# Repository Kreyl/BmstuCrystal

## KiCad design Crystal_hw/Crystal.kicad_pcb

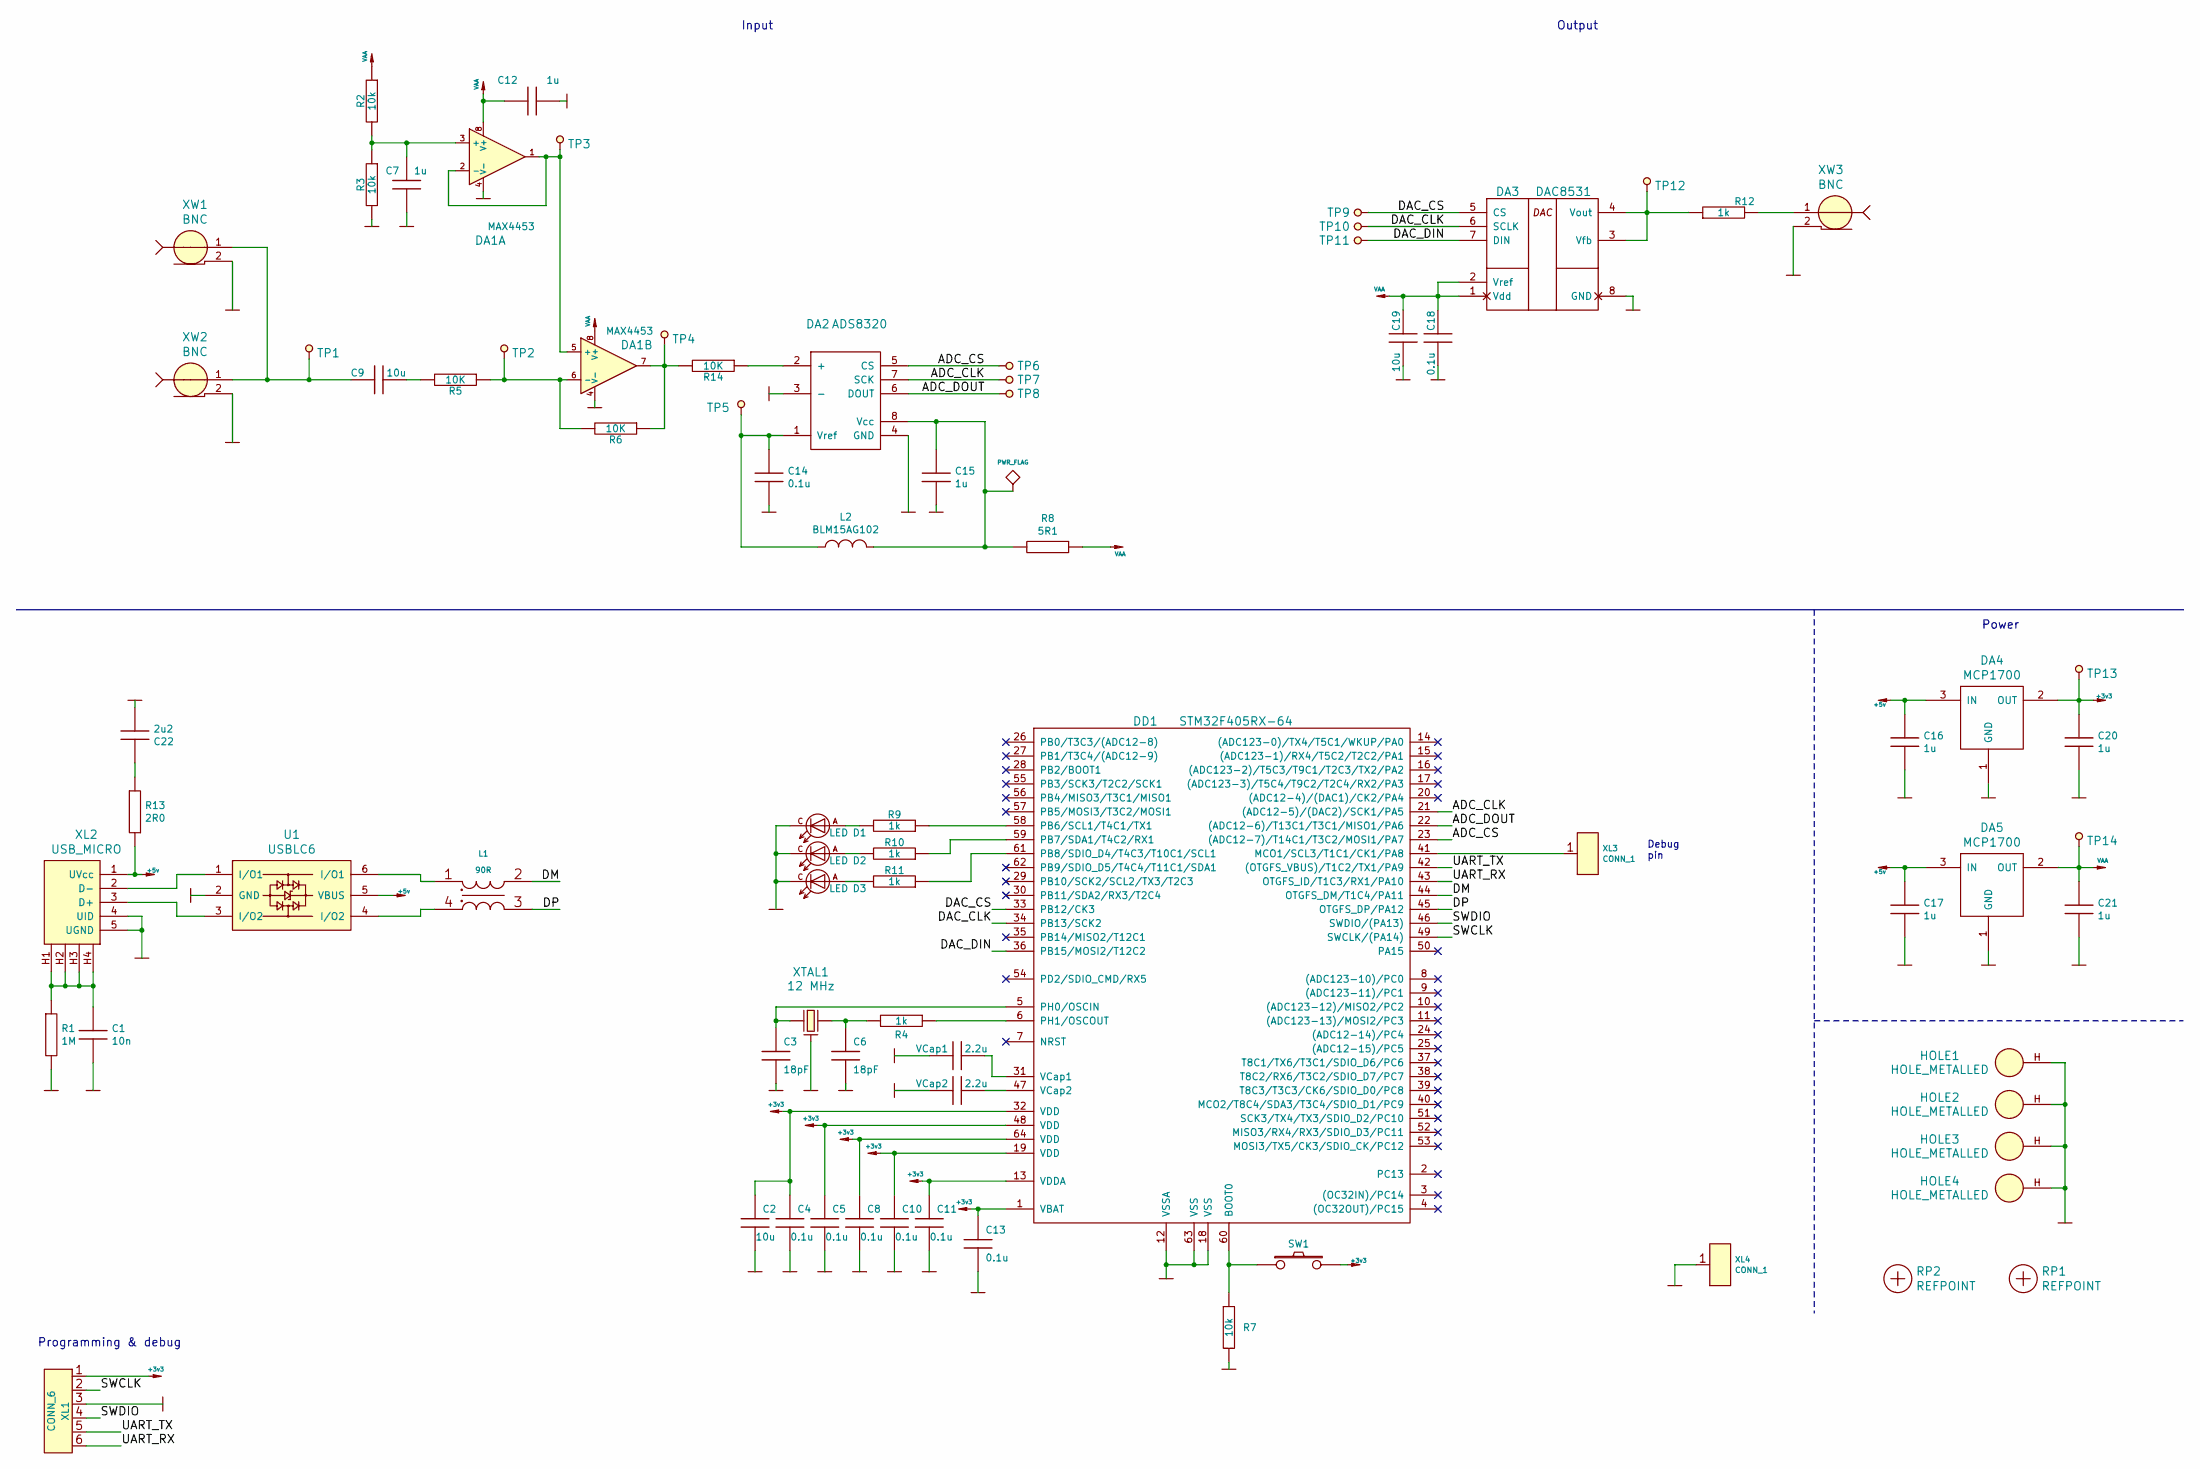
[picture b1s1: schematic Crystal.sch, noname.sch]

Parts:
C1: 10n; CAP_0603
C2, C9, C19: 10u; CAP_0603
C3, C6: 18pF; CAP_0603
C4, C5, C8, C10, C11, C13, C14, C18: 0.1u; CAP_0603
C7, C12, C15, C16, C17, C20, C21: 1u; CAP_0603
C22: 2u2; CAP_0603
D1, D2, D3: LED; LED_0603
DA1: MAX4453; SOT23-8
DA2: ADS8320; MSOP8
DA3: DAC8531; MSOP8
DA4, DA5: MCP1700; SOT23-3A
DD1: STM32F405RX-64; LQFP64
HOLE1, HOLE2, HOLE3, HOLE4: HOLE_METALLED; Hole3_5_out6mm
L1: 90R; DLW21SN
L2: BLM15AG102; IND_0402
R1: 1M; RES_0603
R2, R3, R7: 10k; RES_0603
R4, R9, R10, R11, R12: 1k; RES_0603
R5, R6, R14: 10K; RES_0603
R8: 5R1; RES_0603
R13: 2R0; RES_0603
RP1, RP2: REFPOINT; REF_POINT_1MM
SW1: BUTTON_H; BTN_4x4_SMD
TP1, TP2, TP3, TP4, TP5, TP6, TP7, TP8, TP9, TP10, TP11, TP12, TP13, TP14: TESTPOINT; TESTPOINT_1MM
U1: USBLC6; SOT23-6
VCap1, VCap2: 2.2u; CAP_0603
XL1: CONN_6; PLS-6
XL2: USB_MICRO; USBmicro_MOLEX_1050170001
XL3, XL4: CONN_1; PLS-1Rnd
XTAL1: 12 MHz; 03225C4
XW1, XW2, XW3: BNC; BNC2

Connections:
+3v3: C2.1, C4.1, C5.1, C8.1, C10.1, C11.1, C13.1, C20.1, DA4.2 (OUT), DD1.1 (VBAT), DD1.13 (VDDA), DD1.19 (VDD), DD1.32 (VDD), DD1.48 (VDD), DD1.64 (VDD), SW1.2, TP13.1, XL1.1
+5v: C16.1, C17.1, DA4.3 (IN), DA5.3 (IN), R13.2, U1.5 (VBUS), XL2.1 (UVcc)
/ADC_CLK: DA2.7 (SCK), DD1.21 ((ADC12-5)/(DAC2)/SCK1/PA5), TP7.1
/ADC_CS: DA2.5 (CS), DD1.23 ((ADC12-7)/T14C1/T3C2/MOSI1/PA7), TP6.1
/ADC_DOUT: DA2.6 (DOUT), DD1.22 ((ADC12-6)/T13C1/T3C1/MISO1/PA6), TP8.1
/DAC_CLK: DA3.6 (SCLK), DD1.34 (PB13/SCK2), TP10.1
/DAC_CS: DA3.5 (CS), DD1.33 (PB12/CK3), TP9.1
/DAC_DIN: DA3.7 (DIN), DD1.36 (PB15/MOSI2/T12C2), TP11.1
/DM: DD1.44 (OTGFS_DM/T1C4/PA11), L1.2
/DP: DD1.45 (OTGFS_DP/PA12), L1.3
/SWCLK: DD1.49 (SWCLK/(PA14)), XL1.2
/SWDIO: DD1.46 (SWDIO/(PA13)), XL1.4
/UART_RX: DD1.43 (OTGFS_ID/T1C3/RX1/PA10), XL1.6
/UART_TX: DD1.42 ((OTGFS_VBUS)/T1C2/TX1/PA9), XL1.5
GND: C1.2, C2.2, C3.2, C4.2, C5.2, C6.2, C7.1, C8.2, C10.2, C11.2, C12.2, C13.2, C14.2, C15.2, C16.2, C17.2, C18.1, C19.1, C20.2, C21.2, C22.2, D1.C, D2.C, D3.C, DA1.4 (V-), DA2.3 (-), DA2.4 (GND), DA3.8 (GND), DA4.1 (GND), DA5.1 (GND), DD1.12 (VSSA), DD1.18 (VSS), DD1.63 (VSS), HOLE1.H, HOLE2.H, HOLE3.H, HOLE4.H, R1.2, R3.2, R7.2, U1.2 (GND), VCap1.2, VCap2.2, XL1.3, XL2.4 (UID), XL2.5 (UGND), XL4.1, XTAL1.H, XW1.2, XW2.2, XW3.2
unnamed: C1.1, R1.1, XL2.H1, XL2.H2, XL2.H3, XL2.H4
unnamed: C3.1, DD1.5 (PH0/OSCIN), XTAL1.1
unnamed: C6.1, R4.2, XTAL1.2
unnamed: C7.2, DA1.3 (+), R2.2, R3.1
unnamed: C9.1, TP1.1, XW1.1, XW2.1
unnamed: C9.2, R5.2
unnamed: C14.1, DA2.1 (Vref), L2.1, TP5.1
unnamed: C15.1, DA2.8 (Vcc), L2.2, R8.2
unnamed: C22.1, R13.1
unnamed: D1.A, R9.2
unnamed: D2.A, R10.2
unnamed: D3.A, R11.2
unnamed: DA1.1, DA1.2 (-), DA1.5 (+), TP3.1
unnamed: DA1.6 (-), R5.1, R6.2, TP2.1
unnamed: DA1.7, R6.1, R14.2, TP4.1
unnamed: DA2.2 (+), R14.1
unnamed: DA3.3 (Vfb), DA3.4 (Vout), R12.1, TP12.1
unnamed: DD1.6 (PH1/OSCOUT), R4.1
unnamed: DD1.31 (VCap1), VCap1.1
unnamed: DD1.41 (MCO1/SCL3/T1C1/CK1/PA8), XL3.1
unnamed: DD1.47 (VCap2), VCap2.1
unnamed: DD1.58 (PB6/SCL1/T4C1/TX1), R9.1
unnamed: DD1.59 (PB7/SDA1/T4C2/RX1), R10.1
unnamed: DD1.60 (BOOT0), R7.1, SW1.1
unnamed: DD1.61 (PB8/SDIO_D4/T4C3/T10C1/SCL1), R11.1
unnamed: L1.1, U1.6 (I/O1)
unnamed: L1.4, U1.4 (I/O2)
unnamed: R12.2, XW3.1
unnamed: U1.1 (I/O1), XL2.2 (D-)
unnamed: U1.3 (I/O2), XL2.3 (D+)
VAA: C12.1, C18.2, C19.2, C21.1, DA1.8 (V+), DA3.1 (Vdd), DA3.2 (Vref), DA5.2 (OUT), R2.1, R8.1, TP14.1

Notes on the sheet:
Input
Output
Power
Programming & debug
Debug pin

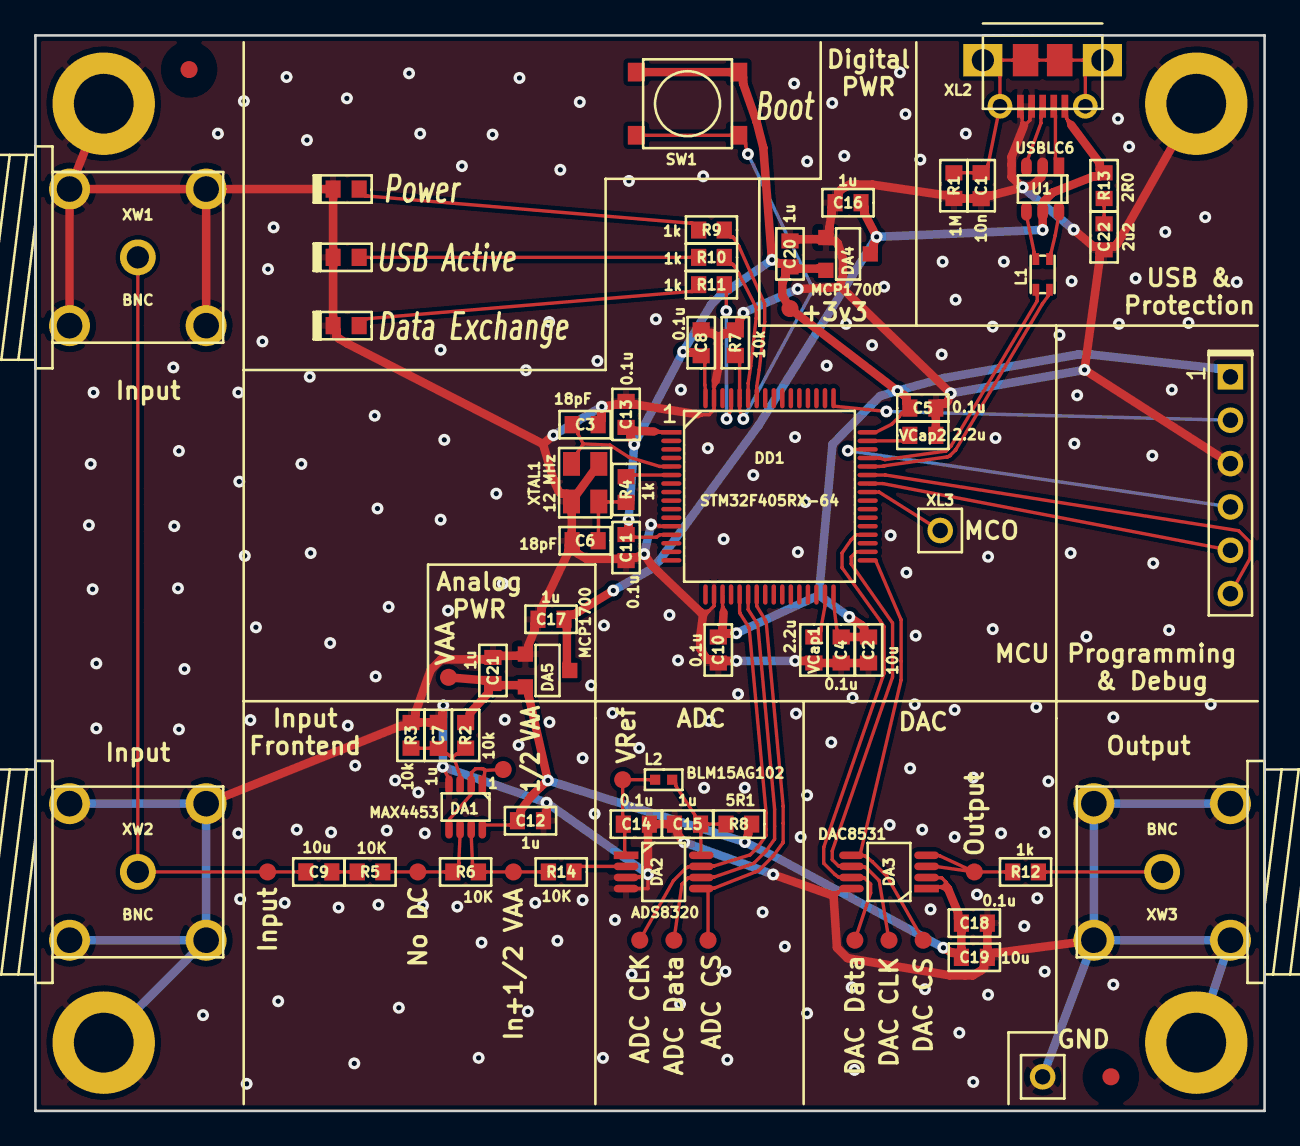
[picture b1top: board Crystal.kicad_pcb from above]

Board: 2 copper layers, 72.0 x 63.0 mm, 79 parts (0 on the bottom side), 46 nets.

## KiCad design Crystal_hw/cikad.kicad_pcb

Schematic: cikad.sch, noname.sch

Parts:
BN1, BN2: BNC
C1, C8, C16, C17, C18, C19, C20, C21: 0.1u
C2, C3, C4, C7, C9, C10, C11, C14, C15, C22: 10u
C5: 0.01u; CAP_0603
C6: 0.1u; CAP_0603
C12, C13: 20pF
C23: 10u; CAP_0603
D1, D2, D3: LED
DA1: GENERIC_8PIN
DA2: DAC8531
DA3: ADS8320
DA4, DA5: LD1117
DD1: STM32F405RX-64
HOLE1, HOLE2, HOLE3, HOLE4: HOLE_METALLED
R1: 10K
R2, R4: 10k
R3: 1k; RES_0603
R5: 200R
R6, R7, R8: 200
R9: 1k
SW1: BUTTON_H
U1: ADG723
VCap1, VCap2: 2.2u
XL1: CONN_3
XL2: USB_MINI_B
XL3: ST_SWD
XTAL1: 12 MHz; CRYSTAL

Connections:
+3.3V: C6.1, C11.2, C16.1, C17.1, C18.1, C19.1, C20.1, C21.1, C22.1, DA4.2 (OUT), DA4.PAD (OUT), DD1.1, DD1.13, DD1.19, DD1.32, DD1.48, DD1.64, SW1.2, SW1.2@1, U1.8, XL3.1 (Vdd)
+5V: C10.2, C14.2, DA4.3 (IN), DA5.3 (IN), XL2.1 (UVcc)
/CLK: DA2.6 (SCLK), DD1.34
/CS: DA2.5 (CS), DD1.33
/CSIN: DA3.5 (CS), DD1.20
/D2: C5.1, U1.6
/DIN: DA2.7 (DIN), DD1.36
/DM: DD1.44, XL2.2 (D-)
/DOUT: DA3.6 (DOUT), DD1.22
/DP: DD1.45, XL2.3 (D+)
/IN1: DD1.8, U1.7
/IN2: DD1.9, U1.3
/RX1: DD1.43, XL1.1
/S1: DA2.3 (Vfb), DA2.4 (Vout), R3.1, U1.1, U1.1@1
/S2_D1: BN1.1, R3.2, U1.2, U1.5
/SCK: DA3.7 (SCK), DD1.21
/SWCLK: DD1.49, XL3.2 (SWCLK)
/SWDIO: DD1.46, XL3.4 (SWDIO)
/TX1: DD1.42, XL1.2 (PM)
GND: BN1.2, BN1.H, BN1.H@1, BN2.2, BN2.H, BN2.H@1, C1.1, C2.2, C3.1, C4.1, C5.2, C6.2, C8.1, C9.1, C10.1, C11.1, C12.2, C13.2, C14.1, C15.1, C16.2, C17.2, C18.2, C19.2, C20.2, C21.2, C22.2, C23.2, D1.C, D2.C, D3.C, DA1.4, DA2.8 (GND), DA3.3 (-), DA3.4 (GND), DA4.1 (GND), DA5.1 (GND), DD1.12, DD1.18, DD1.63, HOLE1.Hle, HOLE2.Hle, HOLE3.Hle, HOLE4.Hle, R4.2, R9.2, SW1.H, U1.4, VCap1.2, VCap2.2, XL1.3, XL2.4 (UGND), XL2.5 (UID), XL2.SHLD, XL3.3 (GND), XTAL1.H, XTAL1.H@1
unnamed: BN2.1, C7.1
unnamed: C7.2, DA1.6, DA1.7, DA3.2 (+)
unnamed: DA1.1, DA1.2, DA1.5
unnamed: DD1.6, R5.1
unnamed: DD1.31, VCap1.1
unnamed: C4.2, DA1.3, R2.2, R4.1
unnamed: DD1.60, R9.1, SW1.1, SW1.1@1
unnamed: DD1.39, R8.1
unnamed: D2.A, R7.2
unnamed: DD1.37, R6.1
unnamed: DD1.47, VCap2.1
unnamed: DD1.38, R7.1
unnamed: D1.A, R6.2
unnamed: C1.2, C2.1, DA3.8 (Vcc), R1.1
unnamed: D3.A, R8.2
unnamed: C13.1, R5.2, XTAL1.2
unnamed: C12.1, DD1.5, XTAL1.1
VAA: C3.2, C8.2, C9.2, C15.2, C23.1, DA1.8, DA2.1 (Vdd), DA2.1@1, DA2.2 (Vref), DA3.1 (Vref), DA3.1@1, DA5.2 (OUT), DA5.PAD (OUT), R1.2, R2.1

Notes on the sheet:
OUT
Power
DEBUG UART
USB
Programming
Connectors
Analog switch

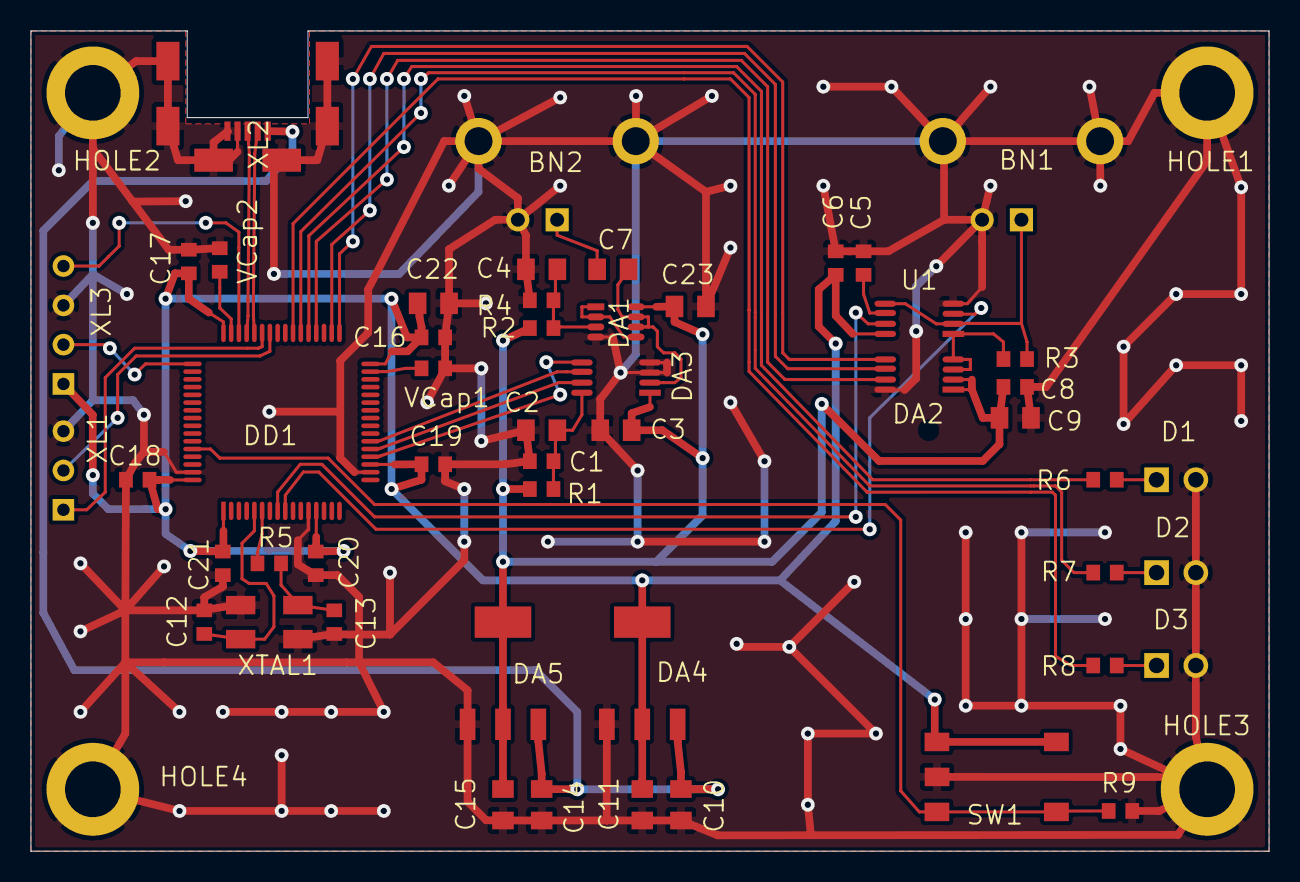
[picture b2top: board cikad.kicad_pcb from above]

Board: 2 copper layers, 80.0 x 53.0 mm, 55 parts (0 on the bottom side), 38 nets.

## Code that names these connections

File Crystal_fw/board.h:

//#pragma once

// ==== General ====
#define APP_NAME            "BmStuCrystal"
// Version of PCB
#define PCB_VER             201904

// MCU type as defined in the ST header.
#define STM32F405xx

// Freq of external crystal if any. Leave it here even if not used.
#define CRYSTAL_FREQ_HZ         12000000

// OS timer settings
#define STM32_ST_IRQ_PRIORITY   2
#define STM32_ST_USE_TIMER      2

#define STM32_DMA_REQUIRED      TRUE    // Leave this macro name for OS

#if 1 // ========================== GPIO =======================================
// EXTI
#define INDIVIDUAL_EXTI_IRQ_REQUIRED    FALSE
// UART
#define UART_GPIO       GPIOA
#define UART_TX_PIN     9
#define UART_RX_PIN     10

#define DEBUG_PIN       GPIOA, 8

// LEDs
#define LED1_PIN        { GPIOB, 6, TIM4, 1, invNotInverted, omPushPull, 255 }
#define LED2_PIN        { GPIOB, 7, TIM4, 2, invNotInverted, omPushPull, 255 }
#define LED3_PIN        { GPIOB, 8, TIM4, 3, invNotInverted, omPushPull, 255 }

// ADC
#define ADC_CLK     	GPIOA, 5
#define ADC_MISO    	GPIOA, 6
#define ADC_CS          GPIOA, 7

// DAC
#define DAC_MOSI    	GPIOB, 15
#define DAC_CS      	GPIOB, 12
#define DAC_CLK     	GPIOB, 13

// USB
#define USB_DM          GPIOA, 11
#define USB_DP          GPIOA, 12
#define USB_AF          AF10

#endif

#if 1 // ========================= Timer =======================================
#define SAMPLING_TMR			TIM5
#define SAMPLING_TMR_IRQ		TIM5_IRQn
#define SAMPLING_TMR_IRQHandler	STM32_TIM5_HANDLER
#endif

#if 1 // =========================== SPI =======================================
// ADC
#define ADC_SPI     	SPI1
// DAC
#define DAC_SPI     	SPI2
#endif

#if 1 // =========================== DMA =======================================
// ==== Uart ====
// Remap is made automatically if required
#define UART_DMA_TX             STM32_DMA_STREAM_ID(2, 7)
#define UART_DMA_RX             STM32_DMA_STREAM_ID(2, 5)
#define UART_DMA_CHNL           4
#define UART_DMA_TX_MODE(Chnl)  (STM32_DMA_CR_CHSEL(Chnl) | DMA_PRIORITY_LOW | STM32_DMA_CR_MSIZE_BYTE | STM32_DMA_CR_PSIZE_BYTE | STM32_DMA_CR_MINC | STM32_DMA_CR_DIR_M2P | STM32_DMA_CR_TCIE)
#define UART_DMA_RX_MODE(Chnl)  (STM32_DMA_CR_CHSEL(Chnl) | DMA_PRIORITY_MEDIUM | STM32_DMA_CR_MSIZE_BYTE | STM32_DMA_CR_PSIZE_BYTE | STM32_DMA_CR_MINC | STM32_DMA_CR_DIR_P2M | STM32_DMA_CR_CIRC)


#define DAC_DMA         STM32_DMA_STREAM_ID(2, 3)
#define DAC_DMA_CHNL    3

// ADC
#define ADC_DMA         STM32_DMA_STREAM_ID(2, 0)
#define ADC_DMA_CHNL    3

#endif

#if 1 // ========================== USART ======================================
#define PRINTF_FLOAT_EN TRUE
#define UART_TXBUF_SZ   4096
#define UART_RXBUF_SZ   99

#define UARTS_CNT       1

#define CMD_UART_PARAMS \
    USART1, UART_GPIO, UART_TX_PIN, UART_GPIO, UART_RX_PIN, \
    UART_DMA_TX, UART_DMA_RX, UART_DMA_TX_MODE(UART_DMA_CHNL), UART_DMA_RX_MODE(UART_DMA_CHNL)

#endif

#if 1 // ========================== USB ========================================
#define HAL_USE_USB                 TRUE
#define HAL_USE_SERIAL_USB			TRUE
/**
 * Serial over USB buffers size.
 * Configuration parameter, the buffer size must be a multiple of
 * the USB data endpoint maximum packet size.
 * The default is 64 bytes for both the transmission and receive buffers.
 */
#define SERIAL_USB_BUFFERS_SIZE     256

#endif

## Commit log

2014-03-06 Copy of Template
2014-03-06 + gitignore
2014-03-06 +adc works begin
2014-03-11 + ADC works
2014-03-12 +DAC works begin
2014-03-13 + DAC works
2014-03-18 +adc + dac
2014-03-21 +Crystal_hw
2014-03-21 KiCAD project edited to add libraries
2014-04-04 + interrupt
2014-04-04 + ADC measurements with DMA
2014-04-06 + Crystal_hw
2014-04-11 + DAC DMA
2014-04-11 + application, evtmsk
2014-09-15 - application, everything moved to main. * small changes all over. + OS Debug features switched on.
2014-09-19 * Descriptors changed => USB connects, but VCP functional still not implemented
2014-09-22 UnhandledControlPacket handled Queue transactions in progress
2014-09-22 pityful attempt to switch to chibi USB driver
2014-09-24 * EP Addr and Indx equaled. * UsbUart transmit works, but crashes soon.
2014-09-26 * TX ZERO PKT works with queue
2014-09-26 * Usb seems to work, proceeding with Cmd reception
2014-09-28 Usb Cmd works
2014-09-28 * Dir structure changed + FIR settings received correctly
2014-09-28 proceeding
2014-09-29 + Terminal Macros file + SetSmplFreq cmd implemented * Timer freq setup modified in accordance with multipliers
2014-09-30 * input DC filtering works + FIR 20th order
2014-09-30 + Start/Stop
2014-10-02 + Set resolution
2014-10-02 + IIR filter: set up, but not working
2014-10-06 IIR works
2014-10-06 * filters corrected, work ok + terminal macroses for filters
2014-10-17 + FPU works correctly
2014-10-17 Filter seems working
2014-10-20 + FirFloat works
2014-10-20 * Terminal macro: FIR switched to float
2014-10-20 Float filters only
2014-10-20 + All-Pass filter + Notch filter
2014-10-20 + Notch filter completed
2014-10-20 * Cmd slightly changed
2014-10-22 Moved to ST's Virtual COM port VID/PID
2014-10-22 + Crystal sw
2014-11-06 * SetLineCoding did not work, now works
2014-11-07 * LEDs renamed * LEDs behavior changed
2014-11-08 Constructors added to appease C++ Checker.
2014-11-08 + Last version of C# Software added
2015-10-24 * Switch to Chibios 3.0, nothing works save UART
2015-10-25 + Shell + Cmd processing from both UART and USB
2015-10-25 Minor
2015-10-25 + ADC & DAC + Sampling + Direct ADC-to-DAC
2015-10-25 Release Candidate
2015-12-21 * Shell: Ack \r\n instead of \r\nAck + ADC one-sample buffer to remove glitches + LED Cmd indication * Cmd process using goto instead of return
2018-05-16 + sch v4
2019-04-12 HW v20190412 in progress
2019-05-09 switching to newer framework
2019-05-10 + Usb works Starting ADC
2019-05-10 Bypass works
2019-05-10 + Release
2019-06-03 Release
2020-04-26 + Overflow added
2020-04-26 * Better check for overflow
